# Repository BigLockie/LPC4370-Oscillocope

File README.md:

# 34 MSa/s Dual Channel Oscillscope
A custom design dual channel USB-C oscilloscope built around the NXP LPC4370 (100 pin TFBGA) intended to output to a Python-based graphical display on a connected computer driven by PyQtGraph. The oscilloscope was designed for the Oregon State University Junior Design II course (ECE 342), the project took place over a 10 week term. 

### Figures:

# Contributors:
Luke Neilson,
Griffin Ziemer, and
Cooper Holm

## Key Features:
* Dual Channel Simulatnuous Sample Rate: 34MSa/s.
* Vertical Resolution: 12-bits.
* Bandwidth: 1MHz.
* Input Voltage Range: +/- 10V with a 10x attenuation probe, +/- 1V with a 1x attenuation probe.
* AC/DC Coupling: Hardware AC/DC coupling using a photo relay to bypass a 100nF capacitor.
* Power: Powered entirely via a standard USB 2.0 connection (nominally drawing 180mA), with a visible LED power indicator.
* User Interface: High-speed display which responds to user input in an average of 0.350 milliseconds

## Hardware Architecture
* Power Block: 5V USB input regulated down to 3.3V digital rail using a TpS79533 LDO. An LM27762 charge pump provides +/- 1.65V rails for some of the Analog Front End op-amps. A 500mV Vref offset is generated off a ferrite bead from the 3.3V line.
* Analog Front End: Incoming signals pass through the coupling and overvoltage protection stages into a variable gain attenuation controlled by TMUX1134 precision analog multiplexers. OPA356 op-amps shift and scale the signals to fit the 100mV to 900mV window required by the LPC4370's ADC.
* Microcontroller: The system uses an LPC4370's Direct Memory Access controller to write 12-bit ADC results into an SRAM buffer without CPU overhead, ensuring maximum throughput.

## Software & Protocol Stack
* Firmware: The backend firmware configures the Analog Front End Gain and AC/DC photorelays at boot. It serializes DMA transfers into packets containing 0xAA start byte, the daya type, sample count, payload and an XOR checksum, transmitting them over a USB CDC link.
* Host Bridge & GUI: A worker thread deserializes incoming packets, verifies the checksum, and translates raw ADC counts into real voltage based on the current user scale. The UI is built using PyQt5 and pyqtgraph. To maximize accessibilty, Channel 1 is rendered in blue and Channel 2 in pink, complying with NCEAS colorblind-safe guidelines.

## Team Work Breakdown
* Luke Neilson: MCU block design, PCB layout (Versions 1 and 2), initial Display blcok design, and Teensy 4.0 backup implementation.
* Griffin Ziemer: User Input GUI, Backend firmware, host bridge protocol serialization/deserialization, and integration of the display.
* Cooper Holm: Power supply block design, Analog Frent End architecture.

## Future Improvements
### To Be Implemented with Current Hardware
* Real time control over the attenuation paths, allowing selection between gain path: 0.256x, 0.833x, 2.566x, and 10x
* Real time control over AC/DC coupling, allowing selection between gain path: 0.256x, 0.833x, 2.566x, and 10x
* Configure PLLs to create an exact 80MHz clock for the ADC to reach the maximum hardware sampling rate
* Flash firmware to the non-volitile memory
### Version 3 of the PCB Improvements
* Minimize digital analog cross talk: The bandwidth was limited because a more aggressive RC filter at the ADC input was required because of the noise from the digital components (LPC 4370 and a 12MHz external clock).
* Shorten the signal path from the analog front end to the ADC.
* Use differential pair drivers to create differential pairs to go from the analog front end to the ADC

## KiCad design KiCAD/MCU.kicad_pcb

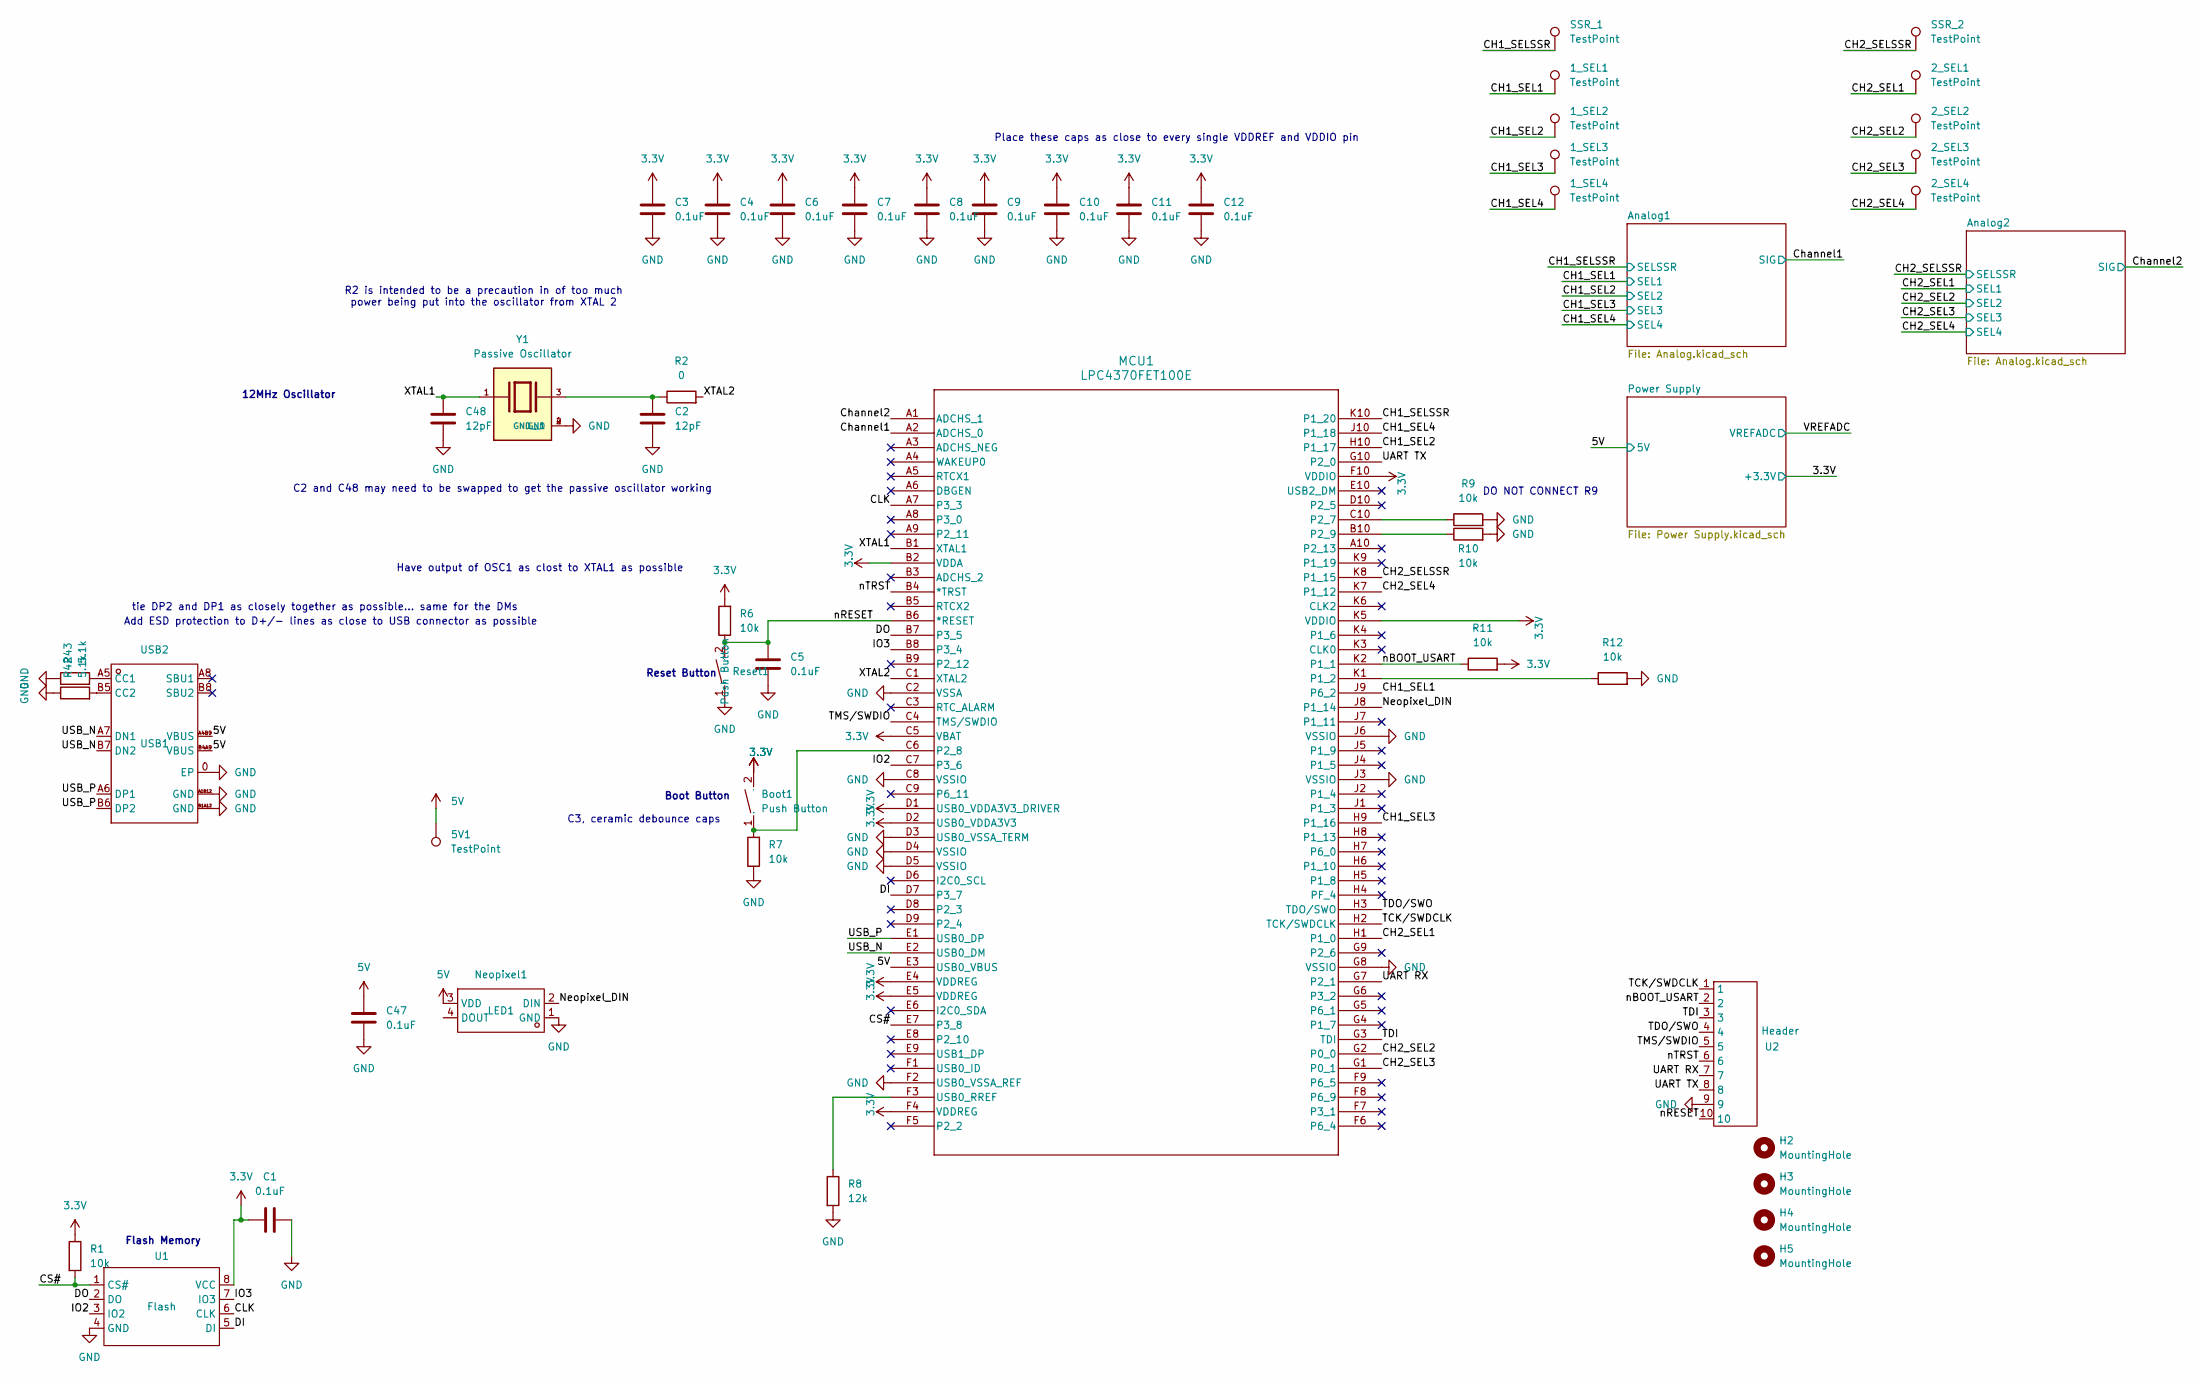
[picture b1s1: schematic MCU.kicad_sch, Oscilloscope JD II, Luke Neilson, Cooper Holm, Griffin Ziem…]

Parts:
1_SEL1, 1_SEL2, 1_SEL3, 1_SEL4, 2_SEL1, 2_SEL2, 2_SEL3, 2_SEL4, 5V1: TestPoint; TestPoint_Pad_1.0x1.0mm
Boot1: Push Button; KEY-SMD; Manufacturer Part -- mixed values --; LCSC Part Name -- mixed values --
C1, C3, C4, C5, C6, C7, C8, C9, C10, C11, C12, C47: 0.1uF; C_0402_1005Metric; Part type Basic
C2, C48: 12pF; C_0402_1005Metric
H2, H3, H4, H5: MountingHole; MountingHole_2.2mm_M2
MCU1: LPC4370FET100E; LPC4370; Part type Extended
Neopixel1: LED1; Neopixel; Manufacturer Part SKC6812RGBW-WS-B; LCSC Part Name 工作电压5V、发光角度120°、灰度调节256级、数据传输频率800Kbps的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
R1, R6, R7, R9, R10, R11, R12: 10k; R_0402_1005Metric; Part type Basic
R2: 0; R_0402_1005Metric
R8: 12k; R_0402_1005Metric; Part type Basic
R42, R43: 5.1k; R_0603_1608Metric; Part type Basic
Reset1: Push Button; KEY-SMD; Manufacturer Part -- mixed values --; LCSC Part Name -- mixed values --
SSR_1, SSR_2: TestPoint; TestPoint_Pad_1.0x1.0mm
U1: Flash; Flash footprint 2.0; Manufacturer Part -- mixed values --; LCSC Part Name -- mixed values --
U2: Header; PinHeader_2x05_P2.54mm_Vertical
USB2: USB1; USB2.0; Manufacturer Part 161N-4PSD43; LCSC Part Name Type-C 母 弯插
Y1: Passive Oscillator; XTAL_ABM3B-12.000MHZ-10-1-U-T; PARTREV 08.25.15

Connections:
3.3V: Boot1.2, C1.1, C3.2, C4.2, C6.2, C7.2, C8.2, C9.2, C10.2, C11.2, C12.2, MCU1.B2 (VDDA), MCU1.C5 (VBAT), MCU1.D1 (USB0_VDDA3V3_DRIVER), MCU1.D2 (USB0_VDDA3V3), MCU1.E4 (VDDREG), MCU1.E5 (VDDREG), MCU1.F4 (VDDREG), MCU1.F10 (VDDIO), MCU1.K5 (VDDIO), R1.1, R6.2, R11.2, U1.8 (VCC); also elsewhere on the board
5V: 5V1.1 (1_1), C47.1, MCU1.E3 (USB0_VBUS), Neopixel1.3 (VDD), USB2.A4B9 (VBUS), USB2.B4A9 (VBUS); also elsewhere on the board
/CH1_SEL1: 1_SEL1.1 (1_1), MCU1.J9 (P6_2); also elsewhere on the board
/CH1_SEL2: 1_SEL2.1 (1_1), MCU1.H10 (P1_17); also elsewhere on the board
/CH1_SEL3: 1_SEL3.1 (1_1), MCU1.H9 (P1_16); also elsewhere on the board
/CH1_SEL4: 1_SEL4.1 (1_1), MCU1.J10 (P1_18); also elsewhere on the board
/CH1_SELSSR: MCU1.K10 (P1_20), SSR_1.1 (1_1); also elsewhere on the board
/CH2_SEL1: 2_SEL1.1 (1_1), MCU1.H1 (P1_0); also elsewhere on the board
/CH2_SEL2: 2_SEL2.1 (1_1), MCU1.G2 (P0_0); also elsewhere on the board
/CH2_SEL3: 2_SEL3.1 (1_1), MCU1.G1 (P0_1); also elsewhere on the board
/CH2_SEL4: 2_SEL4.1 (1_1), MCU1.K7 (P1_12); also elsewhere on the board
/CH2_SELSSR: MCU1.K8 (P1_15), SSR_2.1 (1_1); also elsewhere on the board
/CLK: MCU1.A7 (P3_3), U1.6 (CLK)
/CS#: MCU1.E7 (P3_8), R1.2, U1.1 (CS#)
/Channel1: MCU1.A2 (ADCHS_0); also elsewhere on the board
/Channel2: MCU1.A1 (ADCHS_1); also elsewhere on the board
/DI: MCU1.D7 (P3_7), U1.5 (DI)
/DO: MCU1.B7 (P3_5), U1.2 (DO)
/IO2: MCU1.C7 (P3_6), U1.3 (IO2)
/IO3: MCU1.B8 (P3_4), U1.7 (IO3)
/Neopixel_DIN: MCU1.J8 (P1_14), Neopixel1.2 (DIN)
/TCK/SWDCLK: MCU1.H2 (TCK/SWDCLK), U2.1
/TDI: MCU1.G3 (TDI), U2.3
/TDO/SWO: MCU1.H3 (TDO/SWO), U2.4
/TMS/SWDIO: MCU1.C4 (TMS/SWDIO), U2.5
/UART RX: MCU1.G7 (P2_1), U2.7
/UART TX: MCU1.G10 (P2_0), U2.8
/USB_N: MCU1.E2 (USB0_DM), USB2.A7 (DN1), USB2.B7 (DN2)
/USB_P: MCU1.E1 (USB0_DP), USB2.A6 (DP1), USB2.B6 (DP2)
/XTAL1: C48.1, MCU1.B1 (XTAL1), Y1.1
/XTAL2: MCU1.C1 (XTAL2), R2.2
/nBOOT_USART: MCU1.K2 (P1_1), R11.1, U2.2
/nRESET: C5.2, MCU1.B6 (*RESET), R6.1, Reset1.2, U2.10
/nTRST: MCU1.B4 (*TRST), U2.6
GND: C1.2, C2.2, C3.1, C4.1, C5.1, C6.1, C7.1, C8.1, C9.1, C10.1, C11.1, C12.1, C47.2, C48.2, MCU1.C2 (VSSA), MCU1.C8 (VSSIO), MCU1.D3 (USB0_VSSA_TERM), MCU1.D4 (VSSIO), MCU1.D5 (VSSIO), MCU1.F2 (USB0_VSSA_REF), MCU1.G8 (VSSIO), MCU1.J3 (VSSIO), MCU1.J6 (VSSIO), Neopixel1.1 (GND), R7.1, R8.2, R9.2, R10.2, R12.2, R42.1, R43.1, Reset1.1 (GND), U1.4 (GND), U2.9, USB2.0 (EP), USB2.A1B12 (GND), USB2.B1A12 (GND), Y1.2 (GND), Y1.4 (GND__1); also elsewhere on the board
unnamed: Boot1.1 (GND), MCU1.C6 (P2_8), R7.2
unnamed: C2.1, R2.1, Y1.3
unnamed: MCU1.K1 (P1_2), R12.1
unnamed: MCU1.C10 (P2_7), R9.1
unnamed: MCU1.B10 (P2_9), R10.1
unnamed: MCU1.F3 (USB0_RREF), R8.1
unnamed: R43.2, USB2.A5 (CC1)
unnamed: R42.2, USB2.B5 (CC2)

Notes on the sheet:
DO NOT CONNECT R9
Place these caps as close to every single VDDREF and VDDIO pin
Have output of OSC1 as clost to XTAL1 as possible
Boot Button
C3, ceramic debounce caps
Flash Memory
Reset Button
R2 is intended to be a precaution in of too much power being put into the oscillator from XTAL 2
Add ESD protection to D+/- lines as close to USB connector as possible
tie DP2 and DP1 as closely together as possible... same for the DMs
C2 and C48 may need to be swapped to get the passive oscillator working
12MHz Oscillator

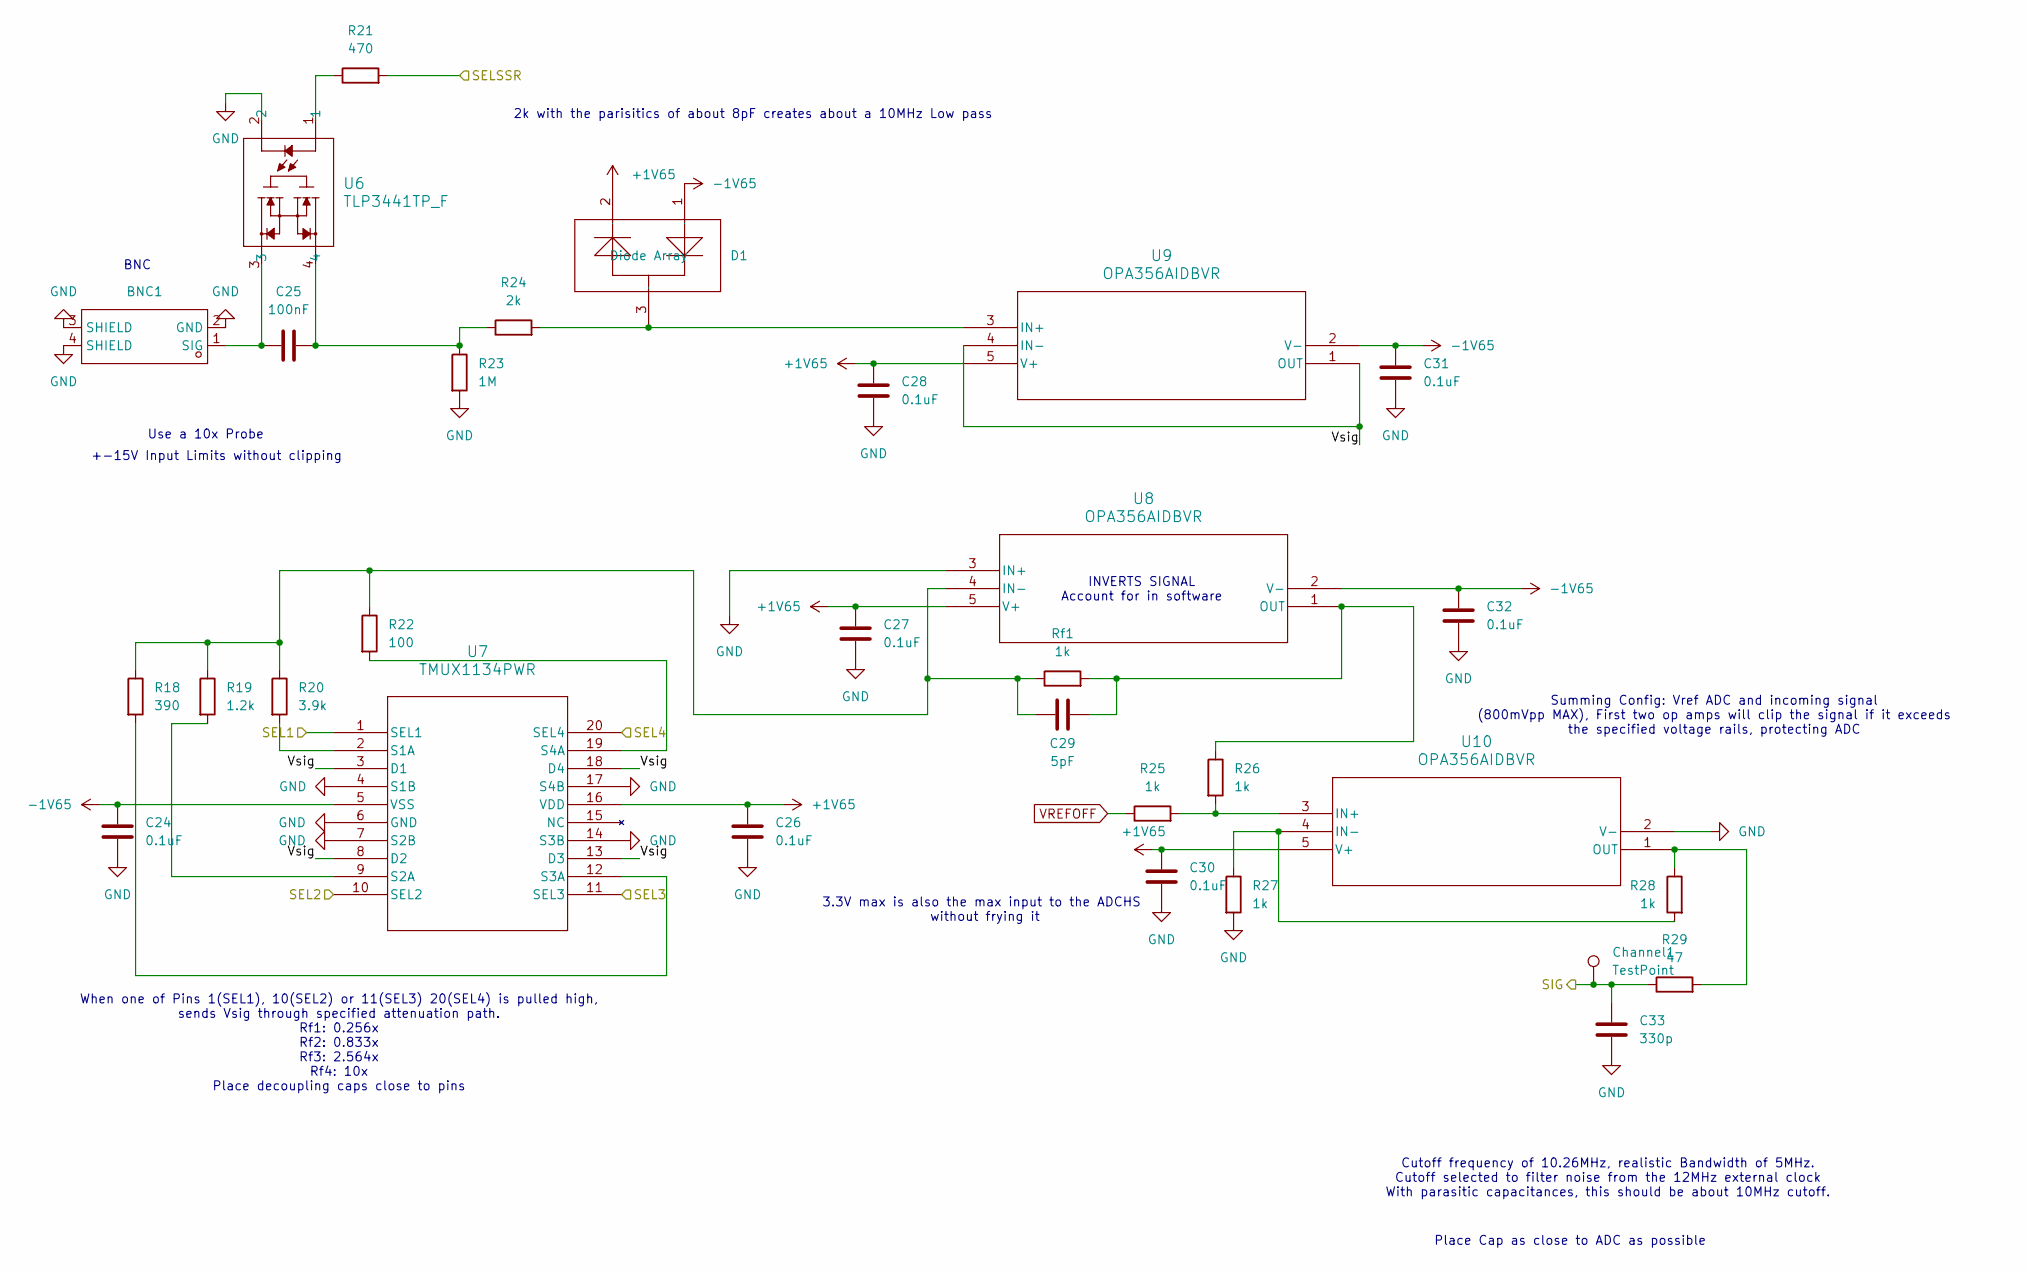
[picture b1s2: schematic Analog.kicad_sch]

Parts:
BNC1: 3GHz; BNC Connector 2.0; Manufacturer Part DOSIN-801-0038; LCSC Part Name 3件套 内孔 BNC 弯头
C24, C26, C27, C28, C30, C31, C32: 0.1uF; C_0402_1005Metric; Part type Basic
C25: 100nF; C_1206_3216Metric; Part type Extended
C29: 5pF; C_0603_1608Metric; Part type Extended
C33: 330p; C_0603_1608Metric; Part type Basic
Channel1: TestPoint; TestPoint_Pad_1.0x1.0mm
D1: Diode Array; SOT-23-3_L2.9-W1.6-P1.90-LS2.8-BR ESD; Manufacturer Part -- mixed values --; LCSC Part Name -- mixed values --
R18: 390; R_0603_1608Metric; Part type Basic
R19: 1.2k; R_0603_1608Metric; Part type Basic
R20: 3.9k; R_0603_1608Metric; Part type Basic
R21: 470; R_0603_1608Metric; Part type Basic
R22: 100; R_0603_1608Metric; Part type Basic
R23: 1M; R_1206_3216Metric; Part type Extended
R24: 2k; R_0805_2012Metric; Part type Basic
R25, R26, R27, R28: 1k; R_0603_1608Metric; Part type Basic
R29: 47; R_0603_1608Metric; Part type Basic
Rf1: 1k; R_0603_1608Metric; Part type Basic
U6: TLP3441TP_F; VSON-4_L1.5-W2.5-P0.80-BL-DCAC-SWITCH; Part type Extended
U7: TMUX1134PWR; TSSOP20_PW_TEX-MUX; Part type Extended
U8, U9, U10: OPA356AIDBVR; DBV5-OPAMP; Part type Extended

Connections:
+1V65: C26.1, C27.1, C28.1, C30.1, D1.2, U7.16 (VDD), U8.5 (V+), U9.5 (V+), U10.5 (V+); also elsewhere on the board
-1V65: C24.1, C31.1, C32.1, D1.1, U7.5 (VSS), U8.2 (V-), U9.2 (V-); also elsewhere on the board
/Analog1/Vsig: U7.3 (D1), U7.8 (D2), U7.13 (D3), U7.18 (D4), U9.1 (OUT), U9.4 (IN-)
/CH1_SEL1: U7.1 (SEL1); also elsewhere on the board
/CH1_SEL2: U7.10 (SEL2); also elsewhere on the board
/CH1_SEL3: U7.11 (SEL3); also elsewhere on the board
/CH1_SEL4: U7.20 (SEL4); also elsewhere on the board
/CH1_SELSSR: R21.2; also elsewhere on the board
/Channel1: C33.1, Channel1.1 (1_1), R29.1; also elsewhere on the board
GND: BNC1.2 (GND), BNC1.3 (SHIELD), BNC1.4 (SHIELD), C24.2, C26.2, C27.2, C28.2, C30.2, C31.2, C32.2, C33.2, R23.2, R27.2, U6.2, U7.4 (S1B), U7.6 (GND), U7.7 (S2B), U7.14 (S3B), U7.17 (S4B), U8.3 (IN+), U10.2 (V-); also elsewhere on the board
unnamed: BNC1.1 (SIG), C25.1, U6.3
unnamed: C25.2, R23.1, R24.1, U6.4
unnamed: R21.1, U6.1
unnamed: R20.2, U7.2 (S1A)
unnamed: R19.2, U7.9 (S2A)
unnamed: R18.2, U7.12 (S3A)
unnamed: R22.2, U7.19 (S4A)
unnamed: C29.2, R18.1, R19.1, R20.1, R22.1, Rf1.1, U8.4 (IN-)
unnamed: C29.1, R26.1, Rf1.2, U8.1 (OUT)
unnamed: D1.3, R24.2, U9.3 (IN+)
unnamed: R25.2, R26.2, U10.3 (IN+)
unnamed: R27.1, R28.2, U10.4 (IN-)
unnamed: R28.1, R29.2, U10.1 (OUT)
VREFOFF: R25.1; also elsewhere on the board

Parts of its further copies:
BNC2: 3GHz; BNC Connector 2.0; Manufacturer Part DOSIN-801-0038; LCSC Part Name 3件套 内孔 BNC 弯头
C34, C36, C37, C38, C40, C41, C42: 0.1uF; C_0402_1005Metric; Part type Basic
C35: 100nF; C_1206_3216Metric; Part type Extended
C39: 5pF; C_0603_1608Metric; Part type Extended
C43: 330p; C_0603_1608Metric; Part type Basic
D2: Diode Array; SOT-23-3_L2.9-W1.6-P1.90-LS2.8-BR ESD; Manufacturer Part -- mixed values --; LCSC Part Name -- mixed values --
R30: 390; R_0603_1608Metric; Part type Basic
R31: 1.2k; R_0603_1608Metric; Part type Basic
R32: 3.9k; R_0603_1608Metric; Part type Basic
R33: 470; R_0603_1608Metric; Part type Basic
R34: 100; R_0603_1608Metric; Part type Basic
R35: 1M; R_1206_3216Metric; Part type Extended
R36: 2k; R_0805_2012Metric; Part type Basic
R37, R38, R39, R40: 1k; R_0603_1608Metric; Part type Basic
R41: 47; R_0603_1608Metric; Part type Basic
Rf2: 1k; R_0603_1608Metric; Part type Basic
TP12: TestPoint; TestPoint_Pad_1.0x1.0mm
U11: TLP3441TP_F; VSON-4_L1.5-W2.5-P0.80-BL-DCAC-SWITCH; Part type Extended
U12: TMUX1134PWR; TSSOP20_PW_TEX-MUX; Part type Extended
U13, U14, U15: OPA356AIDBVR; DBV5-OPAMP; Part type Extended

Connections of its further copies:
+1V65: C36.1, C37.1, C38.1, C40.1, D2.2, U12.16 (VDD), U13.5 (V+), U14.5 (V+), U15.5 (V+); also elsewhere on the board
-1V65: C34.1, C41.1, C42.1, D2.1, U12.5 (VSS), U13.2 (V-), U14.2 (V-); also elsewhere on the board
/Analog2/Vsig: U12.3 (D1), U12.8 (D2), U12.13 (D3), U12.18 (D4), U14.1 (OUT), U14.4 (IN-)
/CH2_SEL1: U12.1 (SEL1); also elsewhere on the board
/CH2_SEL2: U12.10 (SEL2); also elsewhere on the board
/CH2_SEL3: U12.11 (SEL3); also elsewhere on the board
/CH2_SEL4: U12.20 (SEL4); also elsewhere on the board
/CH2_SELSSR: R33.2; also elsewhere on the board
/Channel2: C43.1, R41.1, TP12.1 (1_1); also elsewhere on the board
GND: BNC2.2 (GND), BNC2.3 (SHIELD), BNC2.4 (SHIELD), C34.2, C36.2, C37.2, C38.2, C40.2, C41.2, C42.2, C43.2, R35.2, R39.2, U11.2, U12.4 (S1B), U12.6 (GND), U12.7 (S2B), U12.14 (S3B), U12.17 (S4B), U13.3 (IN+), U15.2 (V-); also elsewhere on the board
unnamed: BNC2.1 (SIG), C35.1, U11.3
unnamed: C35.2, R35.1, R36.1, U11.4
unnamed: R33.1, U11.1
unnamed: R32.2, U12.2 (S1A)
unnamed: R31.2, U12.9 (S2A)
unnamed: R30.2, U12.12 (S3A)
unnamed: R34.2, U12.19 (S4A)
unnamed: C39.2, R30.1, R31.1, R32.1, R34.1, Rf2.1, U13.4 (IN-)
unnamed: C39.1, R38.1, Rf2.2, U13.1 (OUT)
unnamed: D2.3, R36.2, U14.3 (IN+)
unnamed: R37.2, R38.2, U15.3 (IN+)
unnamed: R39.1, R40.2, U15.4 (IN-)
unnamed: R40.1, R41.2, U15.1 (OUT)
VREFOFF: R37.1; also elsewhere on the board

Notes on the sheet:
2k with the parisitics of about 8pF creates about a 10MHz Low pass
When one of Pins 1(SEL1), 10(SEL2) or 11(SEL3) 20(SEL4) is pulled high, sends Vsig through specified attenuation path. Rf1: 0.256x Rf2: 0.833x Rf3: 2.564x Rf4: 10x Place decoupling caps close to pins
3.3V max is also the max input to the ADCHS without frying it
Place Cap as close to ADC as possible
Cutoff frequency of 10.26MHz, realistic Bandwidth of 5MHz. Cutoff selected to filter noise from the 12MHz external clock With parasitic capacitances, this should be about 10MHz cutoff.
+-15V Input Limits without clipping
BNC
Summing Config: Vref ADC and incoming signal (800mVpp MAX), First two op amps will clip the signal if it exceeds the specified voltage rails, protecting ADC
INVERTS SIGNAL Account for in software
Use a 10x Probe

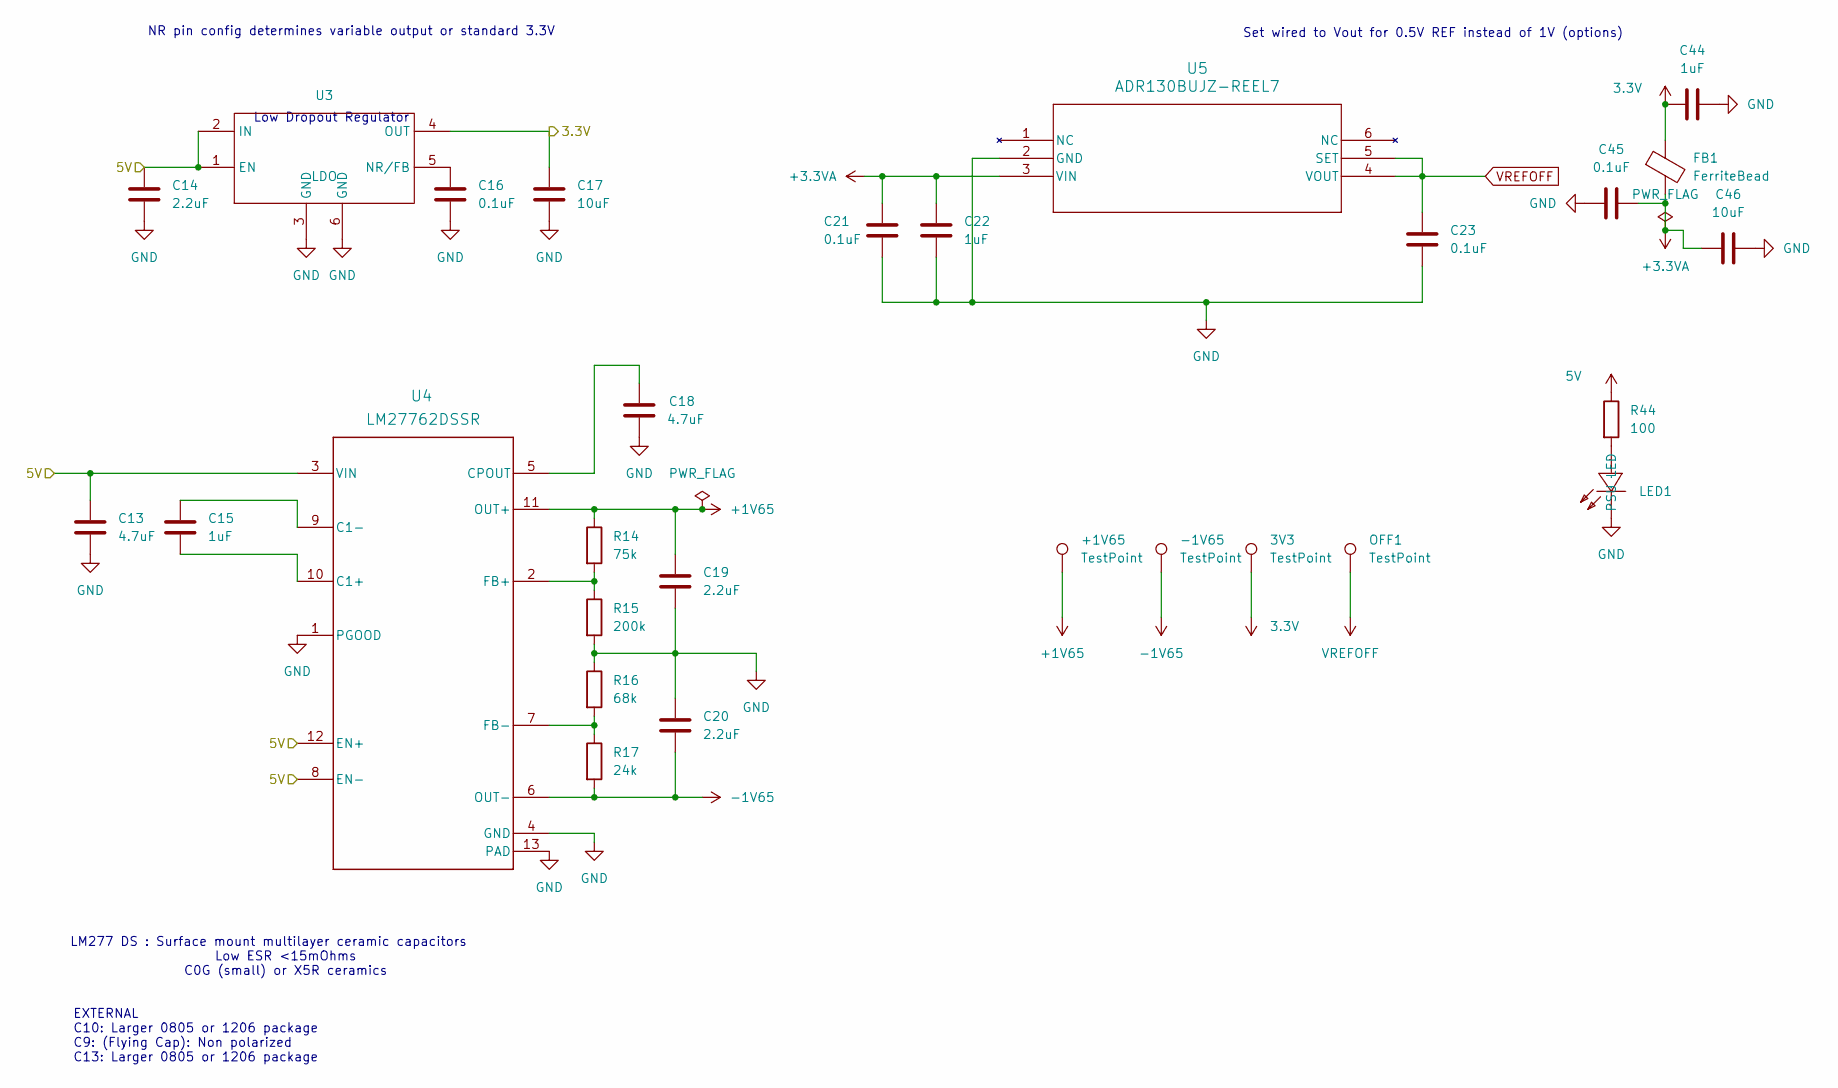
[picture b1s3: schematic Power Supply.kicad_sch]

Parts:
3V3: TestPoint; TestPoint_Pad_1.0x1.0mm
+1V65: TestPoint; TestPoint_Pad_1.0x1.0mm
-1V65: TestPoint; TestPoint_Pad_1.0x1.0mm
C13, C18: 4.7uF; C_0603_1608Metric; Part type Basic
C14, C19, C20: 2.2uF; C_0603_1608Metric; Part type Basic
C15, C22, C44: 1uF; C_0603_1608Metric; Part type Basic
C16, C21, C23, C45: 0.1uF; C_0402_1005Metric; Part type Basic
C17, C46: 10uF; C_0603_1608Metric; Part type Basic
FB1: FerriteBead; L0603 (Ferrite Bead); Part type Basic
LED1: PSU LED; Manufacturer Part KT-0603W; LCSC Part Name 0603 红灯 高亮
OFF1: TestPoint; TestPoint_Pad_1.0x1.0mm
R14: 75k; R_0603_1608Metric; Part type Basic
R15: 200k; R_0603_1608Metric; Part type Basic
R16: 68k; R_0603_1608Metric; Part type Basic
R17: 24k; R_0603_1608Metric; Part type Basic
R44: 100; R_0603_1608Metric; Part type Basic
U3: LDO; SOT-223-6_L6.5-W3.5-P1.27-BL (LDO2.0); Manufacturer Part TPS79501DCQR; LCSC Part Name 具有使能功能的 500mA、低压降稳压器
U4: LM27762DSSR; WSON-12_L3.0-W2.0-P0.50-BL-EP (Charge Pump); Part type Extended
U5: ADR130BUJZ-REEL7; UJ_6_ADI; Part type Extended

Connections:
3.3V: 3V3.1 (1_1), C17.2, C44.1, FB1.1, U3.4 (OUT); also elsewhere on the board
5V: C13.2, C14.2, R44.1, U3.1 (EN), U3.2 (IN), U4.3 (VIN), U4.8 (EN-), U4.12 (EN+); also elsewhere on the board
+1V65: +1V65.1 (1_1), C19.2, R14.1, U4.11 (OUT+); also elsewhere on the board
+3.3VA: C21.2, C22.2, C45.1, C46.1, FB1.2, U5.3 (VIN)
-1V65: -1V65.1 (1_1), C20.1, R17.2, U4.6 (OUT-); also elsewhere on the board
GND: C13.1, C14.1, C16.1, C17.1, C18.1, C19.1, C20.2, C21.1, C22.1, C23.1, C44.2, C45.2, C46.2, LED1.1 (K), R15.2, R16.1, U3.3 (GND), U3.6 (GND), U4.1 (PGOOD), U4.4 (GND), U4.13 (PAD), U5.2 (GND); also elsewhere on the board
unnamed: LED1.2 (A), R44.2
unnamed: C16.2, U3.5 (NR/FB)
unnamed: C15.1, U4.10 (C1+)
unnamed: C15.2, U4.9 (C1-)
unnamed: C18.2, U4.5 (CPOUT)
unnamed: R14.2, R15.1, U4.2 (FB+)
unnamed: R16.2, R17.1, U4.7 (FB-)
VREFOFF: C23.2, OFF1.1 (1_1), U5.4 (VOUT), U5.5 (SET); also elsewhere on the board

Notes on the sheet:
LM277 DS : Surface mount multilayer ceramic capacitors Low ESR <15mOhms C0G (small) or X5R ceramics
Set wired to Vout for 0.5V REF instead of 1V (options)
Low Dropout Regulator
NR pin config determines variable output or standard 3.3V
EXTERNAL C10: Larger 0805 or 1206 package C9: (Flying Cap): Non polarized C13: Larger 0805 or 1206 package

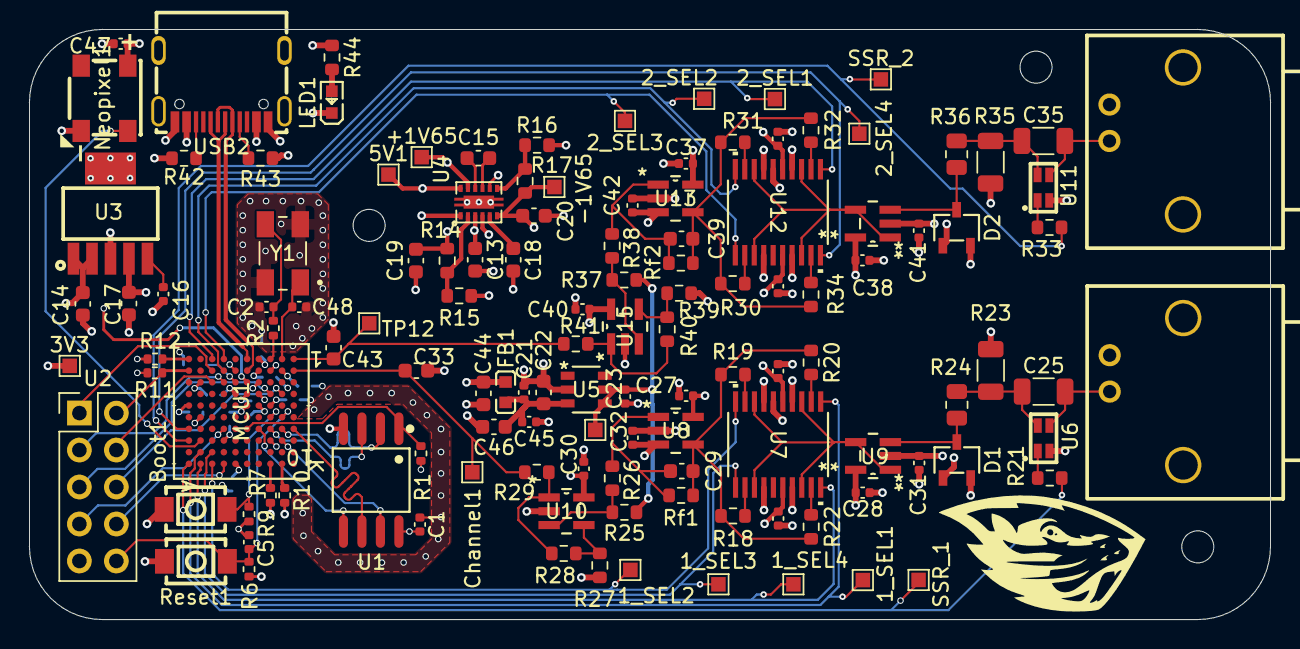
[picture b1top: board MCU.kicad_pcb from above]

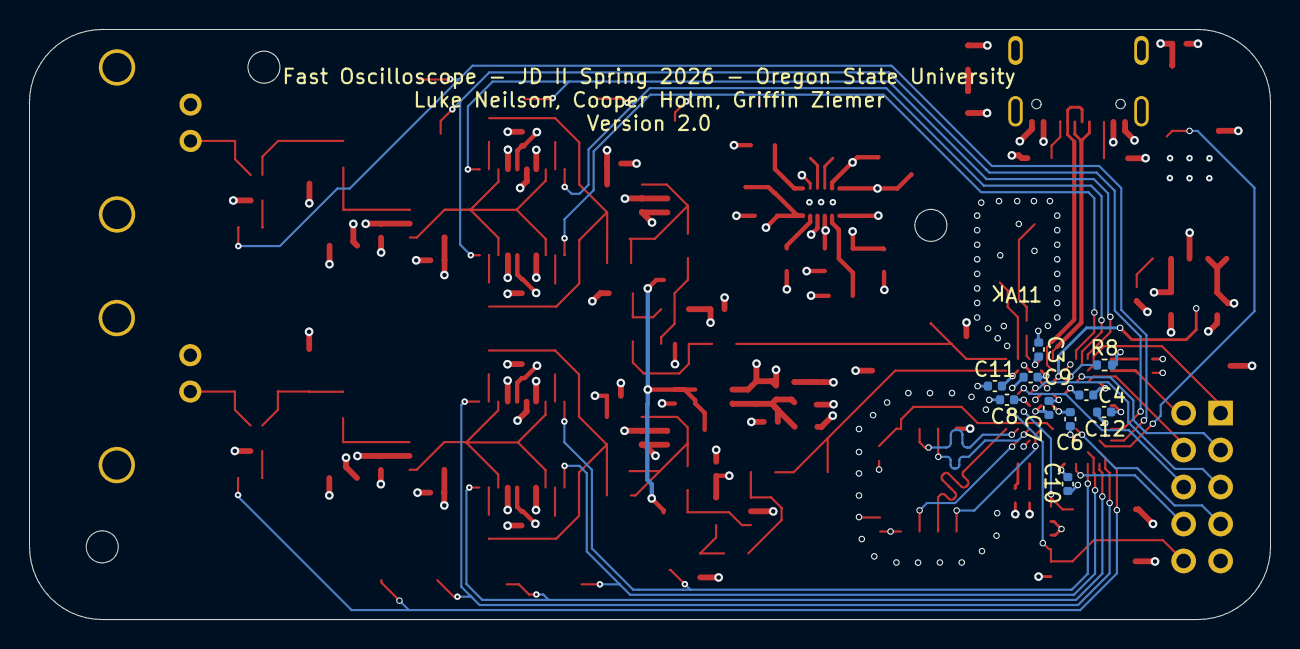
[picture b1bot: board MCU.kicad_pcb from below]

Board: 4 copper layers, 85.3 x 40.5 mm, 137 parts (10 on the bottom side), 82 nets.

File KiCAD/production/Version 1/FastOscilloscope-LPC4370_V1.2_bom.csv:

Designator,Footprint,Quantity,Value,LCSC Part #
"C1, C10, C11, C12, C16, C2, C21, C23, C24, C26, C27, C28, C3, C30, C31, C32, C34, C36, C37, C38, C4, C40, C41, C42, C45, C47, C5, C6, C7, C8, C9",0402,31,0.1uF,
"C13, C18",0603,2,4.7uF,
"C14, C19, C20",0603,3,2.2uF,
"C15, C22, C44",0603,3,1uF,
"C17, C46",0603,2,10uF,
"C33, C43",0603,2,330p,
C48,0603,1,100pF,
"D1, D2",SOT-23-3_L2.9-W1.6-P1.90-LS2.8-BR ESD,2,Diode Array,
FB1,L0603 (Ferrite Bead),1,FerriteBead,
LED1,PSU LED,1,PSU LED,
"R1, R10, R11, R12, R13, R4, R6, R7, R9",0402,9,10k,
R14,0603,1,75k,
R15,0603,1,200k,
R16,0603,1,68k,
R17,0603,1,24k,
"R18, R30",0603,2,390,
"R19, R31, R45",0603,3,1.2k,
"R20, R32",0603,2,3.9k,
"R21, R33",0603,2,470,
"R22, R34, R44",0603,3,100,
"R24, R36",0805,2,2k,
"R25, R26, R27, R28, R37, R38, R39, R40, R46, RF1, RF2",0603,11,1k,
"R29, R41",0603,2,47,
"R42, R43",0603,2,5.1k,
R8,0603,1,12k,
U1,Flash Memory,1,Flash,

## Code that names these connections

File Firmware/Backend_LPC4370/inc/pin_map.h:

/*
 * pin_map.h
 *
 * Named pin defines for the FastOscilloscope LPC4370 board. All values
 * come from the Luke's pin-assignment table (Pin Changes, rev. June 2026).
 *
 * The LPC4370 multiplexes I/O via the System Control Unit (SCU). Each
 * physical pin (e.g. P1_18) selects a function (FUNC0..FUNC7) that maps
 * it to a peripheral. To use a pin as a GPIO we also need to know which
 * GPIO port/bit it lands on after the SCU mapping; the LPC43xx user
 * manual Table 158 lists those.
 *
 * Format used below for GPIO outputs:
 *   <NAME>_PORT, <NAME>_BIT, <NAME>_SCU_PORT, <NAME>_SCU_PIN, <NAME>_SCU_FUNC
 *
 * The SCU_FUNC is whichever FUNC# routes the physical pin to a normal
 * GPIO pad (most LPC43xx pins use FUNC0 or FUNC4 for GPIO).
 */

#ifndef _PIN_MAP_H_
#define _PIN_MAP_H_

/* ----- Channel 1 AFE: gain switch (one-hot) ------------------------- */
/* CH1_SEL1 -> 0.256x   P6_2   -> GPIO3[1]   (FUNC0) */
#define CH1_SEL1_PORT      3
#define CH1_SEL1_BIT       1
#define CH1_SEL1_SCU_PORT  6
#define CH1_SEL1_SCU_PIN   2
#define CH1_SEL1_SCU_FUNC  0

/* CH1_SEL2 -> 0.833x   P1_17  -> GPIO0[12]  (FUNC0) */
#define CH1_SEL2_PORT      0
#define CH1_SEL2_BIT       12
#define CH1_SEL2_SCU_PORT  1
#define CH1_SEL2_SCU_PIN   17
#define CH1_SEL2_SCU_FUNC  0

/* CH1_SEL3 -> 2.564x   P1_16  -> GPIO0[3]   (FUNC0) */
#define CH1_SEL3_PORT      0
#define CH1_SEL3_BIT       3
#define CH1_SEL3_SCU_PORT  1
#define CH1_SEL3_SCU_PIN   16
#define CH1_SEL3_SCU_FUNC  0

/* CH1_SEL4 -> 10x      P1_18  -> GPIO0[13]  (FUNC0) */
#define CH1_SEL4_PORT      0
#define CH1_SEL4_BIT       13
#define CH1_SEL4_SCU_PORT  1
#define CH1_SEL4_SCU_PIN   18
#define CH1_SEL4_SCU_FUNC  0

/* CH1_SELSSR (DC=high, AC=low)   P1_20 -> GPIO0[15] (FUNC0) */
#define CH1_SELSSR_PORT      0
#define CH1_SELSSR_BIT       15
#define CH1_SELSSR_SCU_PORT  1
#define CH1_SELSSR_SCU_PIN   20
#define CH1_SELSSR_SCU_FUNC  0

/* ----- Channel 2 AFE: gain switch (one-hot) ------------------------- */
/* CH2_SEL1 -> 0.256x   P1_0   -> GPIO0[4]   (FUNC0) */
#define CH2_SEL1_PORT      0
#define CH2_SEL1_BIT       4
#define CH2_SEL1_SCU_PORT  1
#define CH2_SEL1_SCU_PIN   0
#define CH2_SEL1_SCU_FUNC  0

/* CH2_SEL2 -> 0.833x   P0_0   -> GPIO0[0]   (FUNC0) */
#define CH2_SEL2_PORT      0
#define CH2_SEL2_BIT       0
#define CH2_SEL2_SCU_PORT  0
#define CH2_SEL2_SCU_PIN   0
#define CH2_SEL2_SCU_FUNC  0

/* CH2_SEL3 -> 2.564x   P0_1   -> GPIO0[1]   (FUNC0) */
#define CH2_SEL3_PORT      0
#define CH2_SEL3_BIT       1
#define CH2_SEL3_SCU_PORT  0
#define CH2_SEL3_SCU_PIN   1
#define CH2_SEL3_SCU_FUNC  0

/* CH2_SEL4 -> 10x      P1_12  -> GPIO1[5]   (FUNC0) */
#define CH2_SEL4_PORT      1
#define CH2_SEL4_BIT       5
#define CH2_SEL4_SCU_PORT  1
#define CH2_SEL4_SCU_PIN   12
#define CH2_SEL4_SCU_FUNC  0

/* CH2_SELSSR (DC=high, AC=low)   P1_15 -> GPIO0[2]  (FUNC0) */
#define CH2_SELSSR_PORT      0
#define CH2_SELSSR_BIT       2
#define CH2_SELSSR_SCU_PORT  1
#define CH2_SELSSR_SCU_PIN   15
#define CH2_SELSSR_SCU_FUNC  0

/* ----- ADCHS analog inputs ----------------------------------------- */
/* ADCHS_0 = Channel 2 input (board net "Channel2") */
/* ADCHS_1 = Channel 1 input (board net "Channel1") */
#define ADCHS_CHANNEL_FOR_CH1   1   /* Ch1 PCB net  -> ADCHS input 1 */
#define ADCHS_CHANNEL_FOR_CH2   0   /* Ch2 PCB net  -> ADCHS input 0 */

/* ----- Misc -------------------------------------------------------- */
/* Neopixel data line                P1_14 -> GPIO1[7]  (FUNC0) */
#define NEOPIXEL_PORT      1
#define NEOPIXEL_BIT       7
#define NEOPIXEL_SCU_PORT  1
#define NEOPIXEL_SCU_PIN   14
#define NEOPIXEL_SCU_FUNC  0

#endif /* _PIN_MAP_H_ */

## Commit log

2026-06-06 Removed old not working files
2026-06-07 Touched up the Read.me
2026-06-07 Editing Read.ME for cadlab
